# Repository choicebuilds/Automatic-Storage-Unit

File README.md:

# StealTheMoon - RoboTechs 2026 Hackathon

## Hardware

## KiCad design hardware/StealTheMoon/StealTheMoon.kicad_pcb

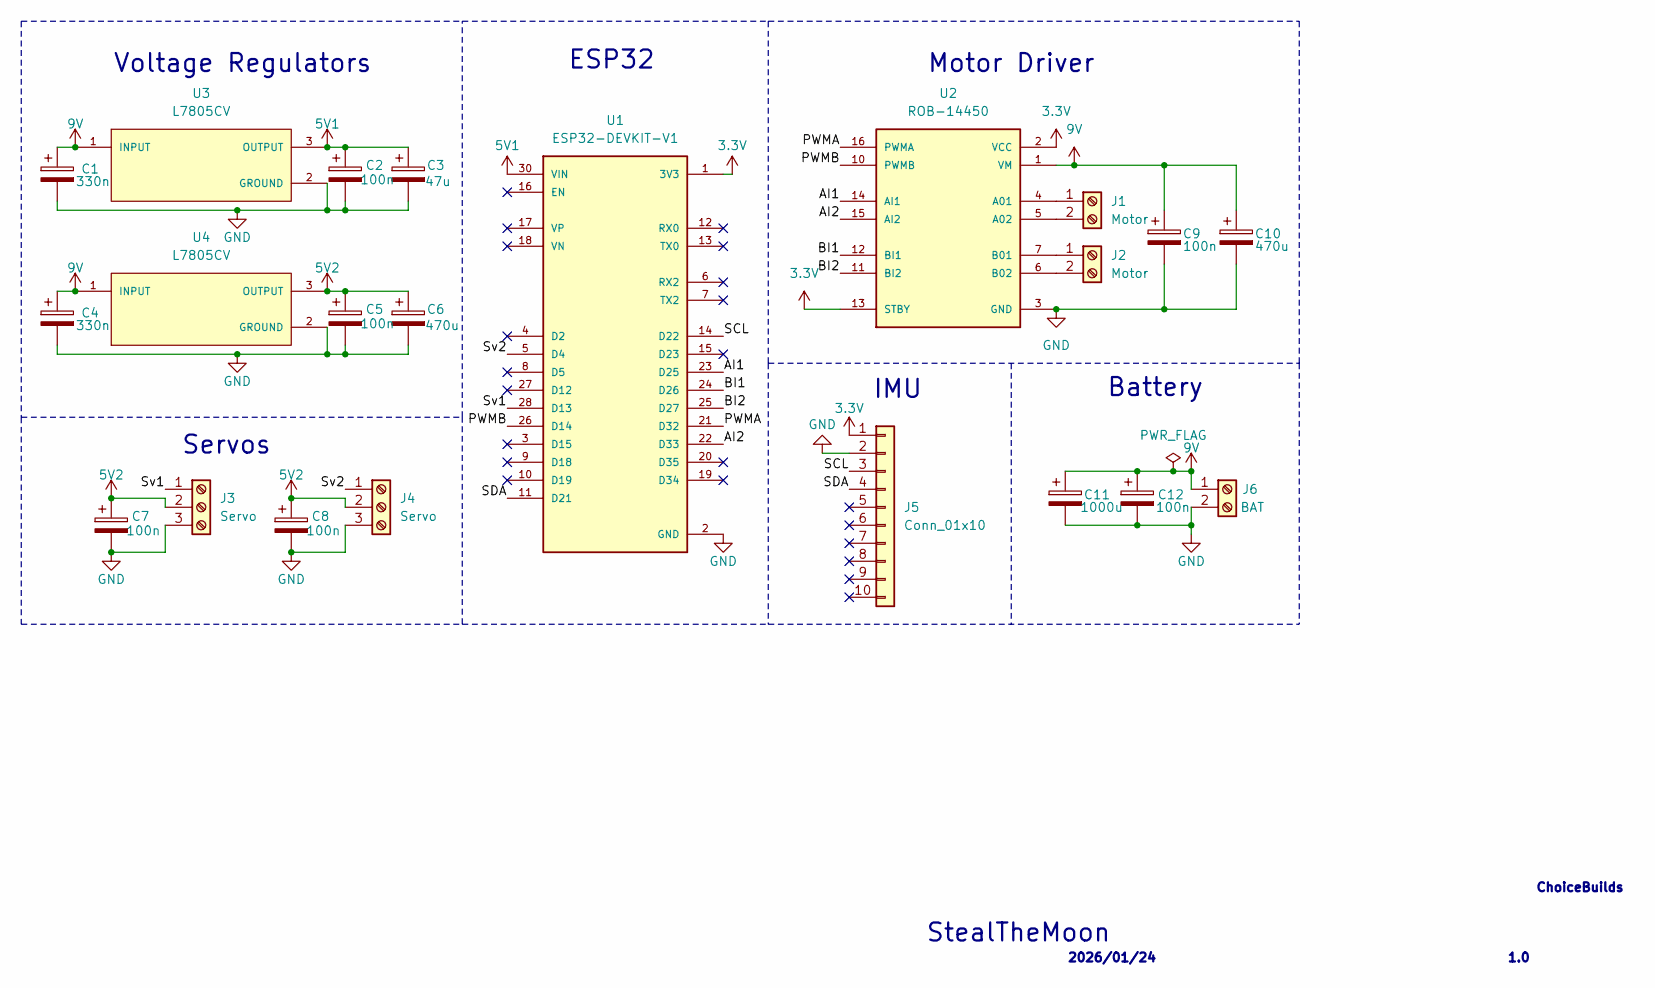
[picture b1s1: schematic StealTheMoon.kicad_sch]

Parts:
C1, C4: 330n; CP_Radial_D5.0mm_P2.50mm
C2, C5, C7, C8, C9, C12: 100n; CP_Radial_D5.0mm_P2.50mm
C3: 47u; CP_Radial_D5.0mm_P2.50mm
C6, C10: 470u; CP_Radial_D8.0mm_P3.50mm
C11: 1000u; CP_Radial_D10.0mm_P5.00mm
J1, J2: Motor; TerminalBlock_MaiXu_MX126-5.0-02P_1x02_P5.00mm
J3, J4: Servo; TerminalBlock_Xinya_XY308-2.54-3P_1x03_P2.54mm_Horizontal
J5: Conn_01x10; PinHeader_1x10_P2.54mm_Vertical
J6: BAT; TerminalBlock_MaiXu_MX126-5.0-02P_1x02_P5.00mm
U1: ESP32-DEVKIT-V1; MODULE_ESP32_DEVKIT_V1; PARTREV N/A
U2: ROB-14450; MODULE_ROB-14450; PARTREV 11-13-17
U3, U4: L7805CV; TO255P1040X460X1968-3; PARTREV 36

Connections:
3.3V: J5.1, U1.1 (3V3), U2.2 (VCC), U2.13 (STBY)
5V1: C2.1, C3.1, U1.30 (VIN), U3.3 (OUTPUT)
5V2: C5.1, C6.1, C7.1, C8.1, J3.2, J4.2, U4.3 (OUTPUT)
9V: C1.1, C4.1, C9.1, C10.1, C11.1, C12.1, J6.1, U2.1 (VM), U3.1 (INPUT), U4.1 (INPUT)
/AI1: U1.23 (D25), U2.14 (AI1)
/AI2: U1.22 (D33), U2.15 (AI2)
/BI1: U1.24 (D26), U2.12 (BI1)
/BI2: U1.25 (D27), U2.11 (BI2)
/PWMA: U1.21 (D32), U2.16 (PWMA)
/PWMB: U1.26 (D14), U2.10 (PWMB)
/SCL: J5.3, U1.14 (D22)
/SDA: J5.4, U1.11 (D21)
/Sv1: J3.1, U1.28 (D13)
/Sv2: J4.1, U1.5 (D4)
GND: C1.2, C2.2, C3.2, C4.2, C5.2, C6.2, C7.2, C8.2, C9.2, C10.2, C11.2, C12.2, J3.3, J4.3, J5.2, J6.2, U1.2 (GND), U1.29 (GND), U2.3 (GND), U2.8 (GND), U2.9 (GND), U3.2 (GROUND), U4.2 (GROUND)
unnamed: J1.1, U2.4 (A01)
unnamed: J1.2, U2.5 (A02)
unnamed: J2.1, U2.7 (B01)
unnamed: J2.2, U2.6 (B02)

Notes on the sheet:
1.0
Servos
Voltage Regulators
ESP32
Motor Driver
2026/01/24
IMU
StealTheMoon
ChoiceBuilds
Battery

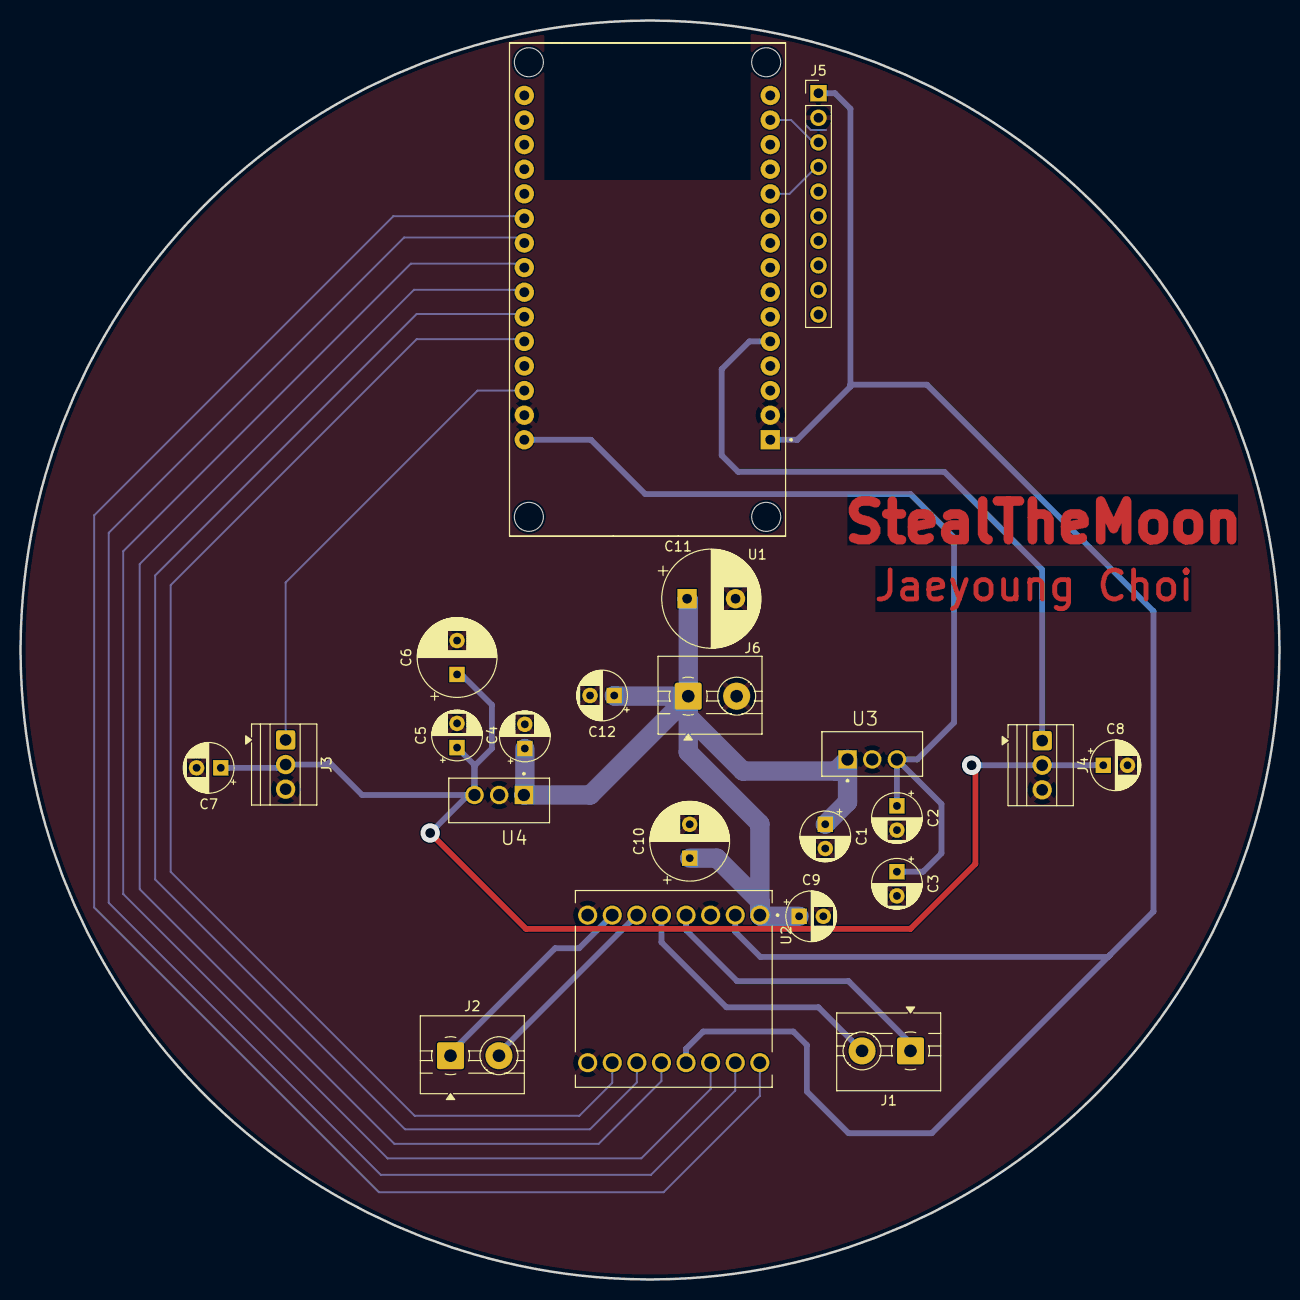
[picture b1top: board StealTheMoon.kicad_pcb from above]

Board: 4 copper layers, 130.0 x 130.0 mm, 22 parts (0 on the bottom side), 19 nets.

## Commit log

2026-01-25 Finish schematic
2026-01-25 Finish layout and generate gbr files for fabrication
2026-01-25 Reroute the PCB to make it smaller
2026-01-25 software added
2026-01-25 Add schematic and layout screenshots
2026-01-25 Add hardware pictures to README.md
2026-02-11 Add pictures of the fabricated layout
2026-05-02 Add remaining pictures
